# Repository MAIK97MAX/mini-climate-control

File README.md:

# MMD Smart Home Solutions – Smart Climate Control

Embedded climate-control system developed as part of our HTL diploma project.

The system uses an ESP32-S3 as the central controller to monitor temperature sensors and control a thermoelectric heating/cooling unit and ventilation fans.

## Features

- ESP32-S3 central controller
- Thermoelectric heating and cooling
- PWM fan control
- Wireless temperature sensors
- Local OLED status display
- Wi-Fi web interface
- USB-C and 12 V power input
- Custom 4-layer PCB

## Repository

This repository contains the hardware design, firmware and related project files.

## Authors

Malik Jukic
David Sayfutdinov
Muhammet Karpuz

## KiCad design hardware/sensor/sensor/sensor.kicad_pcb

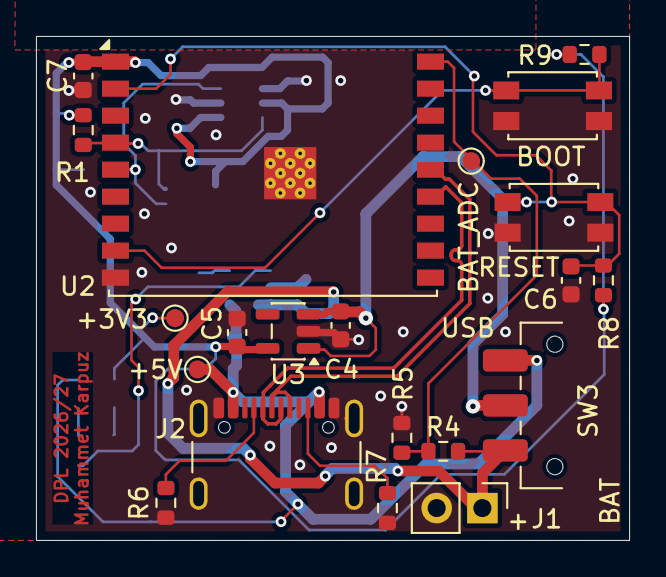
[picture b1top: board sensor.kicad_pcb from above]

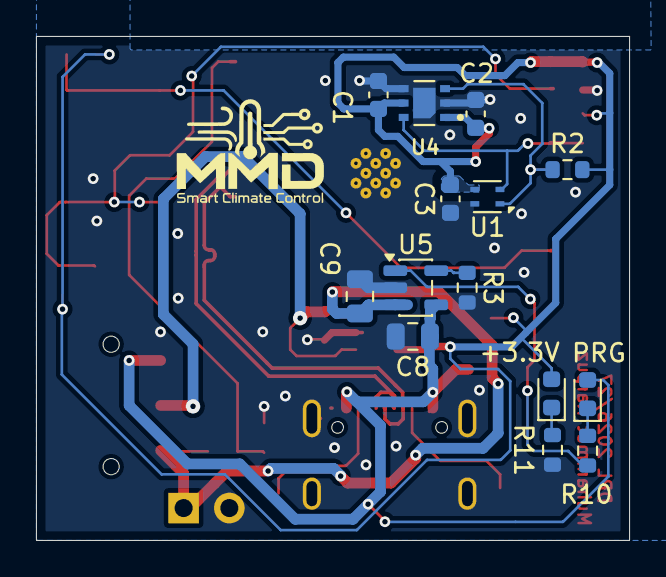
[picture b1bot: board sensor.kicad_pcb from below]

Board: 2 copper layers, 32.9 x 28.0 mm, 35 parts (14 on the bottom side), 18 nets.

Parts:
+3.3V: LED; LED_0603_1608Metric
+3V3, +5V: TestPoint; TestPoint_Pad_D1.0mm
BAT_ADC: TestPoint; TestPoint_Pad_D1.0mm
BOOT: SW_Push; SW_SPST_EVQP2
C1, C2, C4, C5, C6, C7: 1u; C_0603_1608Metric
C3: 100n; C_0603_1608Metric
C8, C9: 10u; C_0805_2012Metric
J1: Conn_01x02_Pin; PinHeader_1x02_P2.54mm_Vertical
J2: USB_C_Receptacle_USB2.0_16P; USB_C_Receptacle_GCT_USB4105-xx-A_16P_TopMnt_Horizontal
PRG: LED; LED_0603_1608Metric
R1, R2: 4.7k; R_0603_1608Metric
R3: 2k; R_0603_1608Metric
R4, R5: 100k; R_0603_1608Metric
R6, R7: 5.1k; R_0603_1608Metric
R8, R9: 10k; R_0603_1608Metric
R10, R11: 470; R_0603_1608Metric
RESET: SW_Push; SW_SPST_EVQP2
SW3: SW_SPDT; SW_SPDT_CK_JS102011SAQN
U1: SHT40; Sensirion_DFN-4_1.5x1.5mm_P0.8mm_SHT4x_NoCentralPad
U2: ESP32-C3-WROOM-02
U3: SL51; SOT-23-5
U4: SGP40; XCDR_SGP40-D-R4
U5: MCP73811T-420I-OT; SOT-23-5

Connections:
+3.3V: +3.3V.2 (A), +3V3.1, C1.1, C2.1, C3.1, C5.1, C7.2, R1.1, R2.1, R8.1, R9.1, U1.3 (VDD), U2.1 (3V3), U3.5 (VOUT), U4.1 (VDD), U4.5 (VDDH)
+5V: +5V.1, C8.1, J2.A4 (VBUS), J2.A9 (VBUS), J2.B4 (VBUS), J2.B9 (VBUS), PRG.2 (A), SW3.3 (C), U5.4 (V_{DD})
/BOOT: BOOT.1, R9.2, U2.8 (IO9)
/Bat+: C9.1, J1.1, R4.1, SW3.1 (A), U5.3 (V_{BAT})
/Bat_ADC: BAT_ADC.1, R4.2, R5.1, U2.18 (IO0)
/CE: R10.2, U5.1 (CE)
/PROG: R3.1, U5.5 (PROG)
/SCL: R1.2, U1.2 (SCL), U2.4 (IO5), U4.6 (SCL)
/SDA: R2.2, U1.1 (SDA), U2.5 (IO6), U4.3 (SDA)
/USB D+: J2.A6 (D+), J2.B6 (D+), U2.14 (IO19)
/USB D-: J2.A7 (D-), J2.B7 (D-), U2.13 (IO18)
GND: BOOT.2, C1.2, C2.2, C3.2, C4.2, C5.2, C6.2, C7.1, C8.2, C9.2, J1.2, J2.A1 (GND), J2.A12 (GND), J2.B1 (GND), J2.B12 (GND), J2.S1 (SHIELD), R3.2, R5.2, R6.2, R7.2, R11.2, RESET.2, U1.4 (VSS), U2.9 (GND), U2.19 (GND), U3.2 (GND), U4.2 (VSS), U4.4 (n/a), U4.7 (pad), U5.2 (V_{SS})
unnamed: PRG.1 (K), R10.1
unnamed: +3.3V.1 (K), R11.1
unnamed: J2.A5 (CC1), R6.1
unnamed: J2.B5 (CC2), R7.1
unnamed: C4.1, SW3.2 (B), U3.1 (VIN), U3.3 (EN)
unnamed: C6.1, R8.2, RESET.1, U2.2 (EN)

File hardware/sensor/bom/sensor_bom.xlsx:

Reference | Qty | Value | DNP | Exclude from BOM | Exclude from Board | Footprint | Datasheet | Von | Im Warenkorb
C1,C4,C5 | 3 | 1u |  |  |  | Capacitor_SMD:C_0603_1608Metric | ~ | schule
C2,C6,C7 | 3 | 1µ |  |  |  | Capacitor_SMD:C_0603_1608Metric | ~ | schule
C3 | 1 | 100n |  |  |  | Capacitor_SMD:C_0603_1608Metric | ~ | schule
J1 | 1 | Conn_01x02_Pin |  |  |  | Connector_PinHeader_2.54mm:PinHeader_1x02_P2.54mm_Vertical | ~
J2 | 1 | USB_C_Receptacle_USB2.0_16P |  |  |  | Connector_USB:USB_C_Receptacle_GCT_USB4105-xx-A_16P_TopMnt_Horizontal | https://www.usb.org/sites/default/files/documents/usb_type-c.zip | schule
R1,R2 | 2 | 4.7k |  |  |  | Resistor_SMD:R_0603_1608Metric | ~ | schule
R4,R5 | 2 | 100k |  |  |  | Resistor_SMD:R_0603_1608Metric | ~ | schule
R6,R7 | 2 | 5.1k |  |  |  | Resistor_SMD:R_0603_1608Metric | ~ | schule
R8,R9 | 2 | 10k |  |  |  | Resistor_SMD:R_0603_1608Metric | ~ | schule
SW1,SW2 | 2 | SW_Push |  |  |  | Button_Switch_SMD:SW_SPST_EVQP2 | ~ | lcsc | x
SW3 | 1 | SW_SPDT |  |  |  | Button_Switch_SMD:SW_SPDT_CK_JS102011SAQN | ~
TP1,TP2,TP3 | 3 | TestPoint |  |  |  | TestPoint:TestPoint_Pad_D1.0mm | ~ | x
U1 | 1 | SHT40 |  |  |  | Sensor_Humidity:Sensirion_DFN-4_1.5x1.5mm_P0.8mm_SHT4x_NoCentralPad | https://sensirion.com/media/documents/33FD6951/624C4357/Data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 | lcsc | x
U2 | 1 | ESP32-C3-WROOM-02 |  |  |  | RF_Module:ESP32-C3-WROOM-02 | https://www.espressif.com/sites/default/files/documentation/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 | lcsc | x
U3 | 1 | AP2112K-3.3 |  |  |  | Package_TO_SOT_SMD:SOT-23-5 | https://www.diodes.com/assets/Datasheets/AP2112.pdf | lcsc | x
U4 | 1 | SGP40 | x |  | x | Sensor_SGP40:XCDR_SGP40-D-R4 |  | lcsc | n.b

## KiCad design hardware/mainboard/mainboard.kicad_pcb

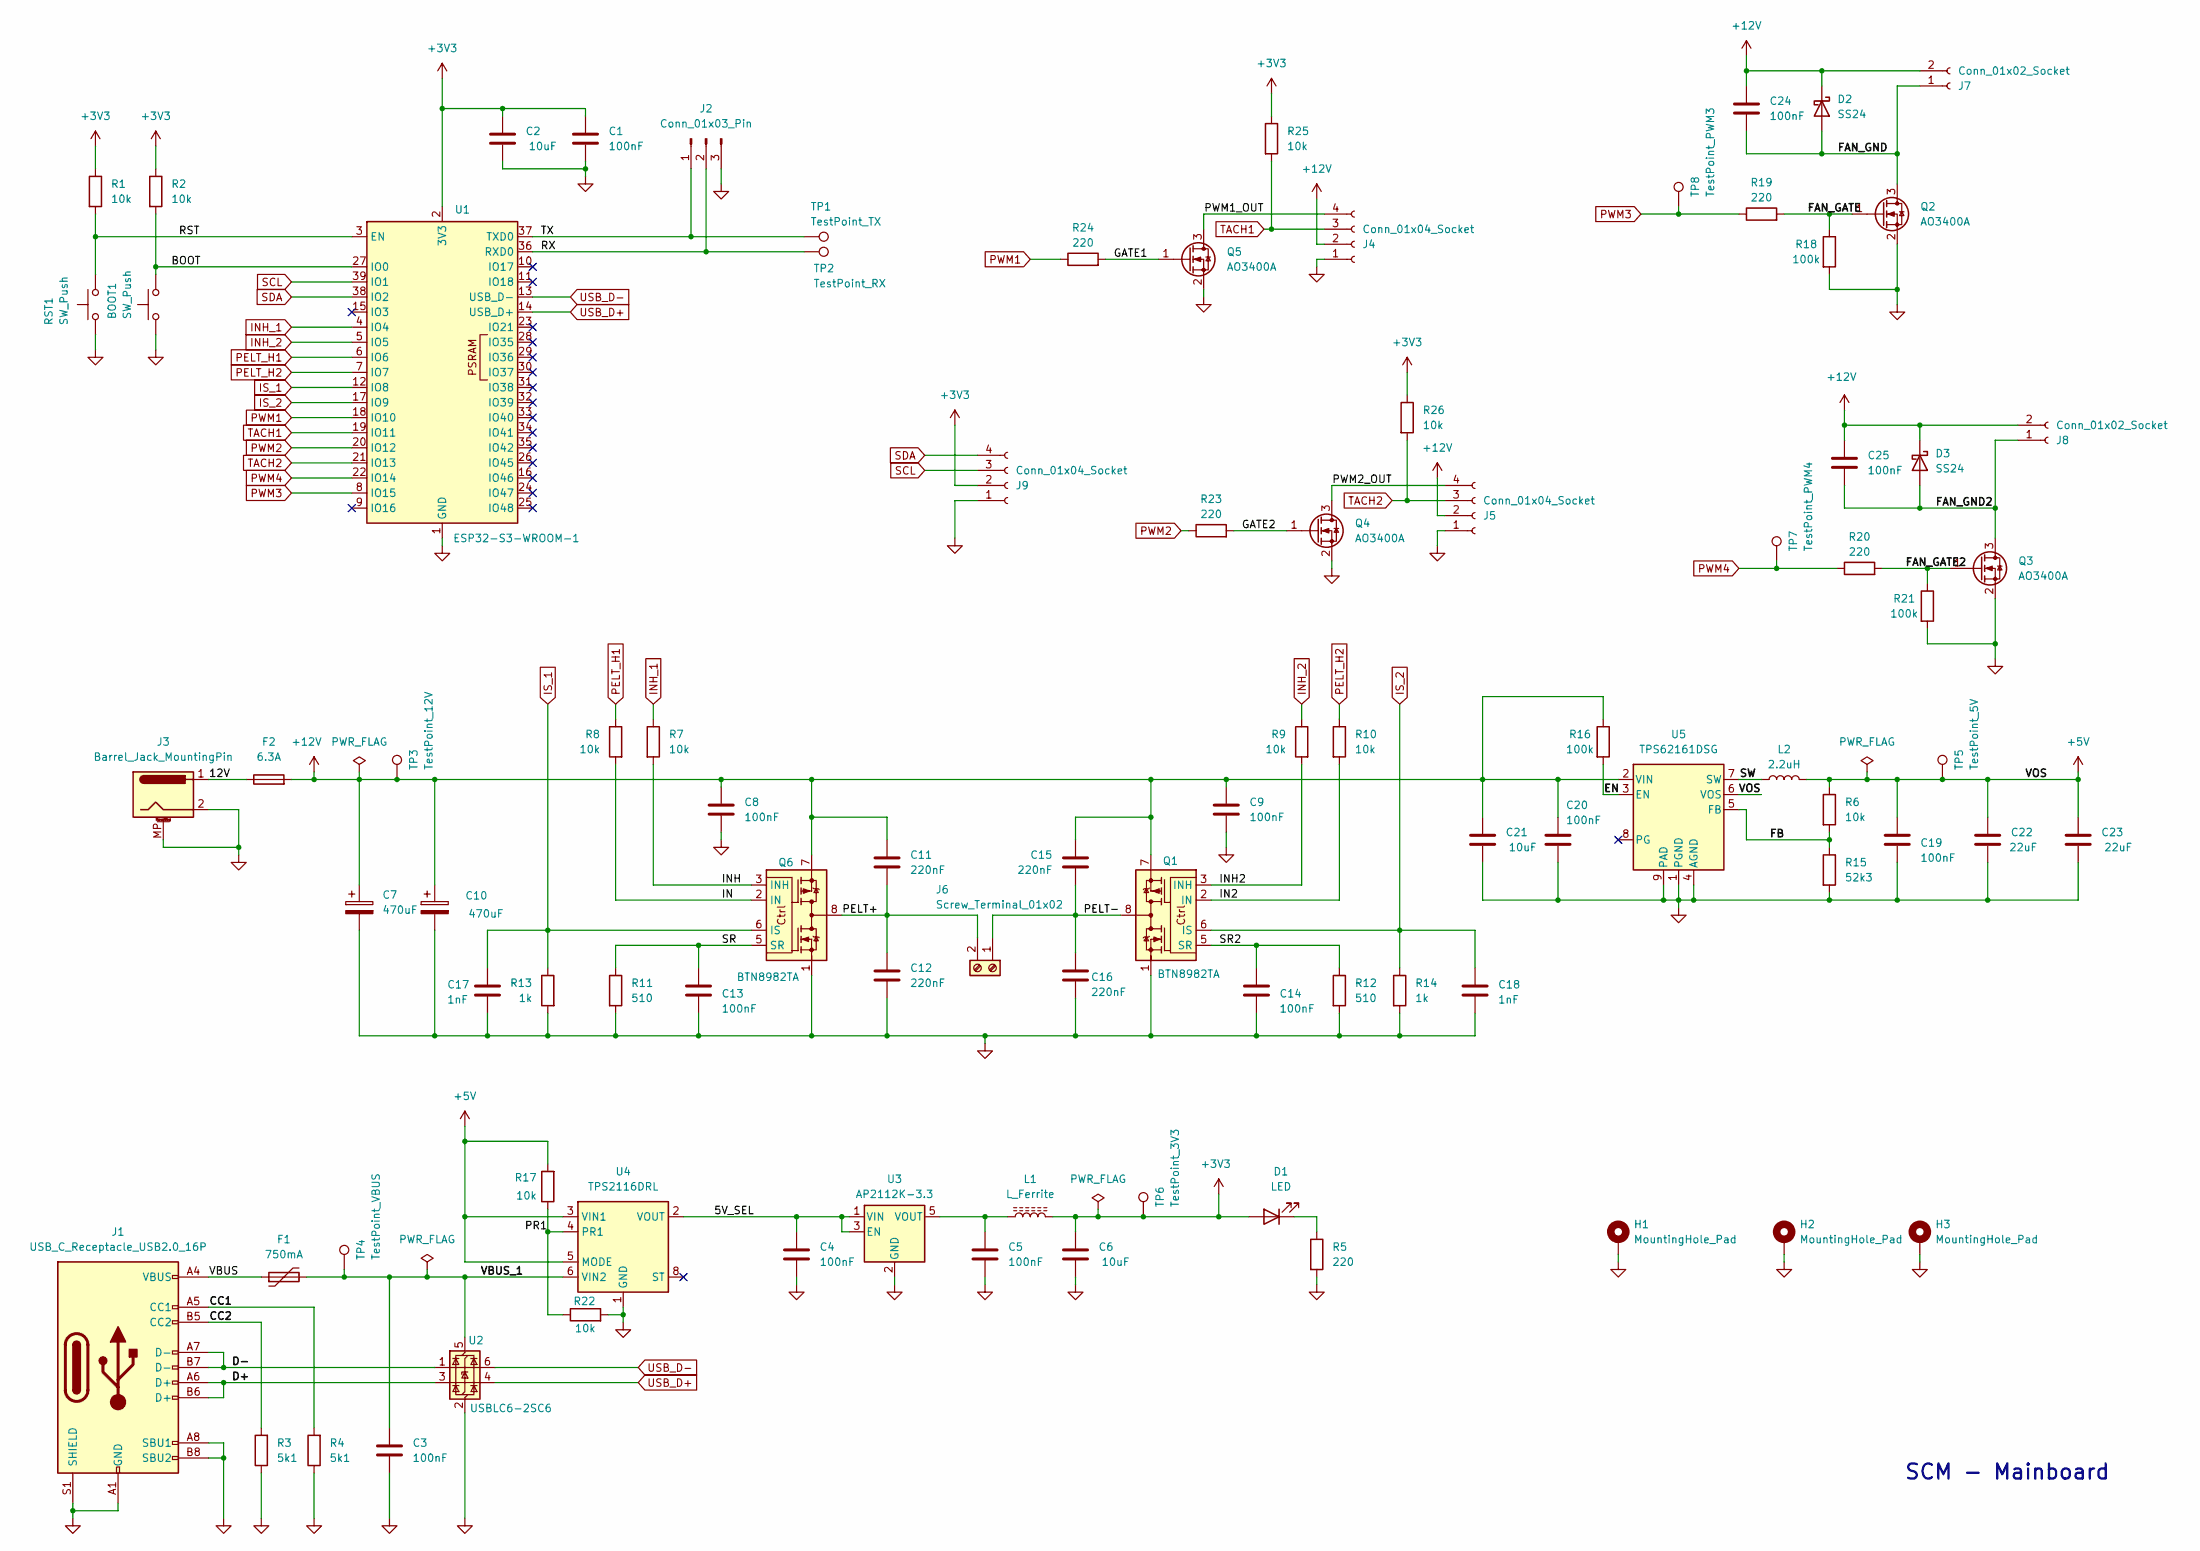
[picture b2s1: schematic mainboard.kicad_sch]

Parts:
BOOT1: SW_Push; SW_SPST_EVQP2_MiddlePushTravel_H2.5mm
C1, C3, C4, C5, C8, C9, C13, C14, C19, C20, C24, C25: 100nF; C_0603_1608Metric
C2, C6, C21: 10uF; C_0805_2012Metric
C7, C10: 470uF; CP_Radial_D10.0mm_P5.00mm
C11, C12, C15, C16: 220nF; C_0603_1608Metric
C17, C18: 1nF; C_0603_1608Metric
C22, C23: 22uF; C_0805_2012Metric
D1: LED; LED_0603_1608Metric
D2, D3: SS24; D_SMA
F1: 750mA; Fuse_1206_3216Metric
F2: 6.3A; Fuse_Littelfuse-NANO2-451_453
H1, H2, H3: MountingHole_Pad; MountingHole_2.2mm_M2_Pad_TopBottom
J1: USB_C_Receptacle_USB2.0_16P; USB_C_Receptacle_G-Switch_GT-USB-7010ASV
J2: Conn_01x03_Pin; PinHeader_1x03_P2.54mm_Vertical
J3: Barrel_Jack_MountingPin; BarrelJack_Horizontal
J4, J5: Conn_01x04_Socket; Molex_KK-254_AE-6410-04A_1x04_P2.54mm_Vertical
J6: Screw_Terminal_01x02; TerminalBlock_CUI_TB007-508-02_1x02_P5.08mm_Horizontal
J7, J8: Conn_01x02_Socket; JST_XH_S2B-XH-A-1_1x02_P2.50mm_Horizontal
J9: Conn_01x04_Socket; PinSocket_1x04_P2.54mm_Vertical
L1: L_Ferrite; L_0603_1608Metric
L2: 2.2uH; L_Coilcraft_LPS3010
Q1, Q6: BTN8982TA; TO-263-7_TabPin8
Q2, Q3, Q4, Q5: AO3400A; SOT-23
R1, R2, R6, R7, R8, R9, R10, R17, R22, R25, R26: 10k; R_0603_1608Metric
R3, R4: 5k1; R_0603_1608Metric
R5, R19, R20, R23, R24: 220; R_0603_1608Metric
R11, R12: 510; R_0603_1608Metric
R13, R14: 1k; R_0603_1608Metric
R15: 52k3; R_0603_1608Metric
R16, R18, R21: 100k; R_0603_1608Metric
RST1: SW_Push; SW_SPST_EVQP2_MiddlePushTravel_H2.5mm
TP1: TestPoint_TX; TestPoint_Pad_D1.0mm
TP2: TestPoint_RX; TestPoint_Pad_D1.0mm
TP3: TestPoint_12V; TestPoint_Pad_D1.0mm
TP4: TestPoint_VBUS; TestPoint_Pad_D1.0mm
TP5: TestPoint_5V; TestPoint_Pad_D1.0mm
TP6: TestPoint_3V3; TestPoint_Pad_D1.0mm
TP7: TestPoint_PWM4; TestPoint_Pad_D1.0mm
TP8: TestPoint_PWM3; TestPoint_Pad_D1.0mm
U1: ESP32-S3-WROOM-1
U2: USBLC6-2SC6; SOT-23-6
U3: AP2112K-3.3; SOT-23-5
U4: TPS2116DRL; SOT-583-8
U5: TPS62161DSG; WSON-8-1EP_2x2mm_P0.5mm_EP0.9x1.6mm_ThermalVias

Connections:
+3V3: C1.1, C2.1, C6.1, D1.2 (A), J9.2, L1.2, R1.1, R2.1, R25.1, R26.1, TP6.1, U1.2 (3V3)
+5V: C19.1, C22.1, C23.1, L2.2, R6.1, R17.2, TP5.1, U4.3 (VIN1), U4.5 (MODE), U5.6 (VOS); also elsewhere on the board
+12V: C7.1, C8.1, C9.1, C10.1, C11.1, C15.1, C20.1, C21.1, C24.1, C25.1, D2.1 (K), D3.1 (K), F2.2, J4.2, J5.2, J7.2, J8.2, Q1.7, Q6.7, R16.1, TP3.1, U5.2 (VIN); also elsewhere on the board
/5V_SEL: C4.1, U3.1 (VIN), U3.3 (EN), U4.2 (VOUT), U4.7 (VOUT)
/12V: F2.1, J3.1
/BOOT: BOOT1.2, R2.2, U1.27 (IO0); also elsewhere on the board
/CC1: J1.A5 (CC1), R4.2
/CC2: J1.B5 (CC2), R3.2
/D+: J1.A6 (D+), J1.B6 (D+), U2.3 (I/O2)
/D-: J1.A7 (D-), J1.B7 (D-), U2.1 (I/O1)
/EN: R16.2, U5.3 (EN)
/FAN_GATE: Q2.1 (G), R18.1, R19.2
/FAN_GATE2: Q3.1 (G), R20.2, R21.1
/FAN_GND: C24.2, D2.2 (A), J7.1, Q2.3 (D)
/FAN_GND2: C25.2, D3.2 (A), J8.1, Q3.3 (D)
/FB: R6.2, R15.1, U5.5 (FB)
/GATE1: Q5.1 (G), R24.2
/GATE2: Q4.1 (G), R23.2
/IN: Q6.2 (IN), R8.2
/IN2: Q1.2 (IN), R10.2
/INH: Q6.3 (INH), R7.2
/INH2: Q1.3 (INH), R9.2
/PELT+: C11.2, C12.1, J6.2, Q6.4, Q6.8
/PELT-: C15.2, C16.1, J6.1, Q1.4, Q1.8
/PR1: R17.1, R22.1, U4.4 (PR1)
/PWM1_OUT: J4.4, Q5.3 (D)
/PWM2_OUT: J5.4, Q4.3 (D)
/RST: R1.2, RST1.2, U1.3 (EN); also elsewhere on the board
/RX: J2.2, TP2.1, U1.36 (RXD0); also elsewhere on the board
/SR: C13.1, Q6.5 (SR), R11.1
/SR2: C14.1, Q1.5 (SR), R12.1
/SW: L2.1, U5.7 (SW)
/TX: J2.1, TP1.1, U1.37 (TXD0); also elsewhere on the board
/VBUS: F1.1, J1.A4 (VBUS), J1.A9 (VBUS), J1.B4 (VBUS), J1.B9 (VBUS)
/VBUS_1: C3.1, F1.2, TP4.1, U2.5 (VBUS), U4.6 (VIN2); also elsewhere on the board
GND: BOOT1.1, C1.2, C2.2, C3.2, C4.2, C5.2, C6.2, C7.2, C8.2, C9.2, C10.2, C12.2, C13.2, C14.2, C16.2, C17.2, C18.2, C19.2, C20.2, C21.2, C22.2, C23.2, H1.1, H2.1, H3.1, J1.A1 (GND), J1.A8 (SBU1), J1.A12 (GND), J1.B1 (GND), J1.B8 (SBU2), J1.B12 (GND), J1.S1 (SHIELD), J2.3, J3.2, J3.3, J3.MP (MountPin), J4.1, J5.1, J9.1, Q1.1, Q2.2 (S), Q3.2 (S), Q4.2 (S), Q5.2 (S), Q6.1, R3.1, R4.1, R5.2, R11.2, R12.2, R13.2, R14.2, R15.2, R18.2, R21.2, R22.2, RST1.1, U1.1 (GND), U1.40 (GND), U1.41 (GND), U2.2 (GND), U3.2 (GND), U4.1 (GND), U5.1 (PGND), U5.4 (AGND), U5.9 (PAD); also elsewhere on the board
INH_1: R7.1, U1.4 (IO4)
INH_2: R9.1, U1.5 (IO5)
IS_1: C17.1, Q6.6 (IS), R13.1, U1.12 (IO8)
IS_2: C18.1, Q1.6 (IS), R14.1, U1.17 (IO9)
unnamed: D1.1 (K), R5.1
unnamed: C5.1, L1.1, U3.5 (VOUT)
PELT_H1: R8.1, U1.6 (IO6)
PELT_H2: R10.1, U1.7 (IO7)
PWM1: R24.1, U1.18 (IO10)
PWM2: R23.1, U1.20 (IO12)
PWM3: R19.1, TP8.1, U1.8 (IO15); also elsewhere on the board
PWM4: R20.1, TP7.1, U1.22 (IO14); also elsewhere on the board
SCL: J9.3, U1.39 (IO1)
SDA: J9.4, U1.38 (IO2)
TACH1: J4.3, R25.2, U1.19 (IO11)
TACH2: J5.3, R26.2, U1.21 (IO13)
USB_D+: U1.14 (USB_D+), U2.4 (I/O2)
USB_D-: U1.13 (USB_D-), U2.6 (I/O1)

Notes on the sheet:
SCM - Mainboard

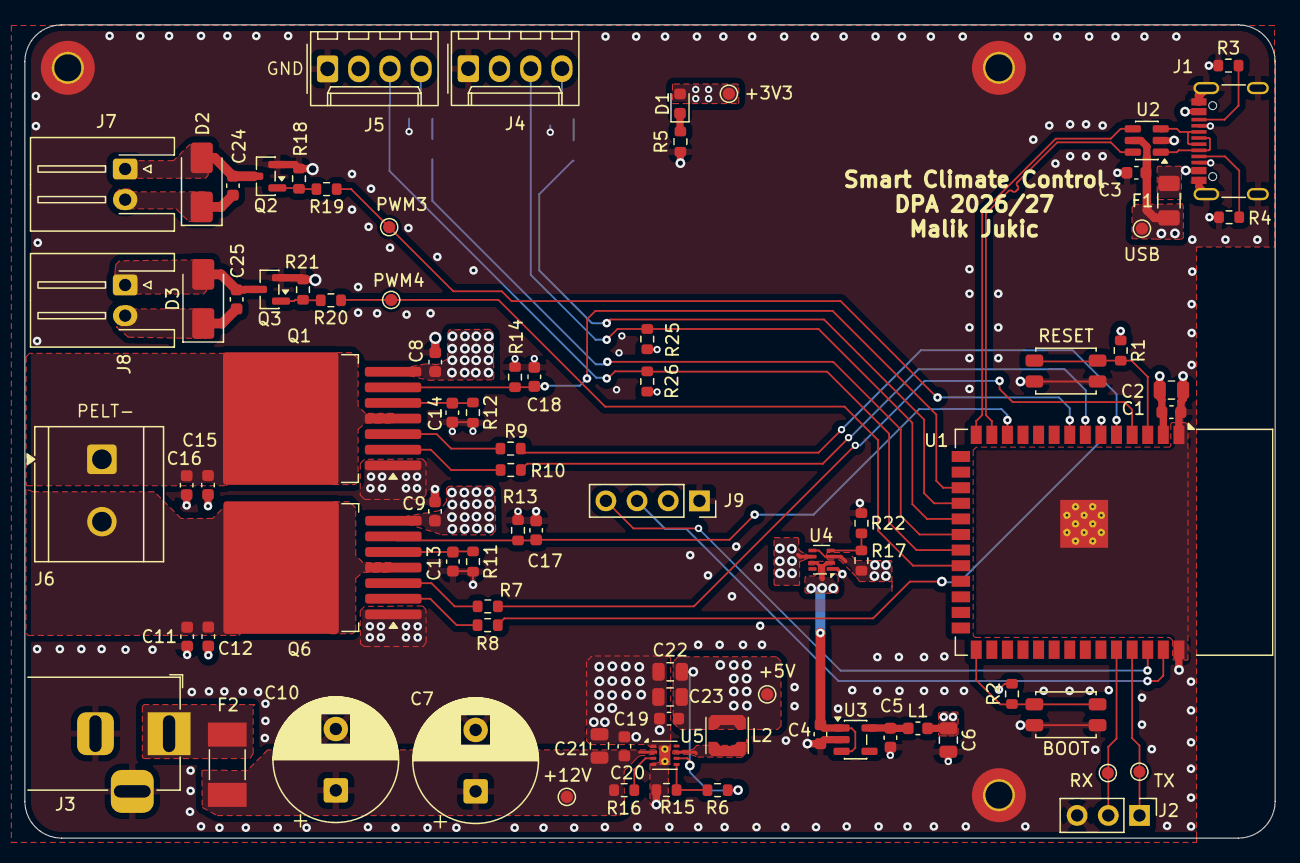
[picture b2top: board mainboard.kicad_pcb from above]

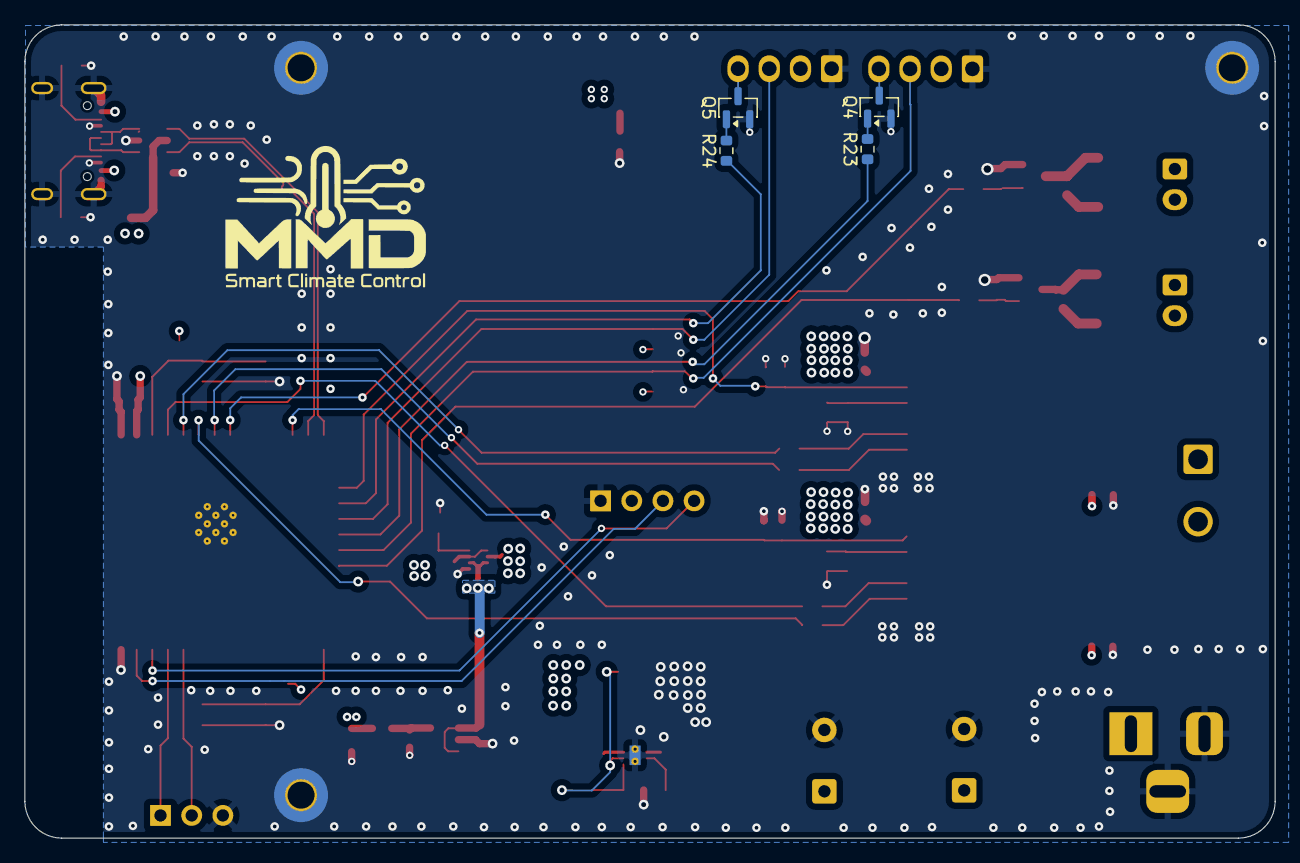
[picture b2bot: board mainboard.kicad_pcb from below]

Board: 4 copper layers, 101.9 x 66.3 mm, 91 parts (4 on the bottom side), 54 nets.

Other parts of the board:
+5V: TestPoint_5V; TestPoint_Pad_D1.0mm
+12V: TestPoint_12V; TestPoint_Pad_D1.0mm
BOOT: SW_Push; SW_SPST_EVQP2_MiddlePushTravel_H2.5mm
PWM3: TestPoint_PWM3; TestPoint_Pad_D1.0mm
PWM4: TestPoint_PWM4; TestPoint_Pad_D1.0mm
RESET: SW_Push; SW_SPST_EVQP2_MiddlePushTravel_H2.5mm
RX: TestPoint_RX; TestPoint_Pad_D1.0mm
TX: TestPoint_TX; TestPoint_Pad_D1.0mm
USB: TestPoint_VBUS; TestPoint_Pad_D1.0mm

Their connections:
+5V: +5V.1; also elsewhere on the board
+12V: +12V.1; also elsewhere on the board
/BOOT: BOOT.2; also elsewhere on the board
/RST: RESET.2; also elsewhere on the board
/RX: RX.1; also elsewhere on the board
/TX: TX.1; also elsewhere on the board
/VBUS_1: USB.1; also elsewhere on the board
GND: BOOT.1, RESET.1; also elsewhere on the board
PWM3: PWM3.1; also elsewhere on the board
PWM4: PWM4.1; also elsewhere on the board
